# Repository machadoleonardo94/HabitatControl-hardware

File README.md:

## Hardware files for running HabitatControl Firmware
### ** Version 1 contains 5 PWM open drain channels, 2 NO relay channels, I2C 1" OLED display and DHT22 humidity and temperature sensor;
### ** Version 3 contains 6 PWM 700mA current limited LED drivers and I2C 1" OLED display
### Both versions are controlled via webserver for schedule of light intensity and data sampling

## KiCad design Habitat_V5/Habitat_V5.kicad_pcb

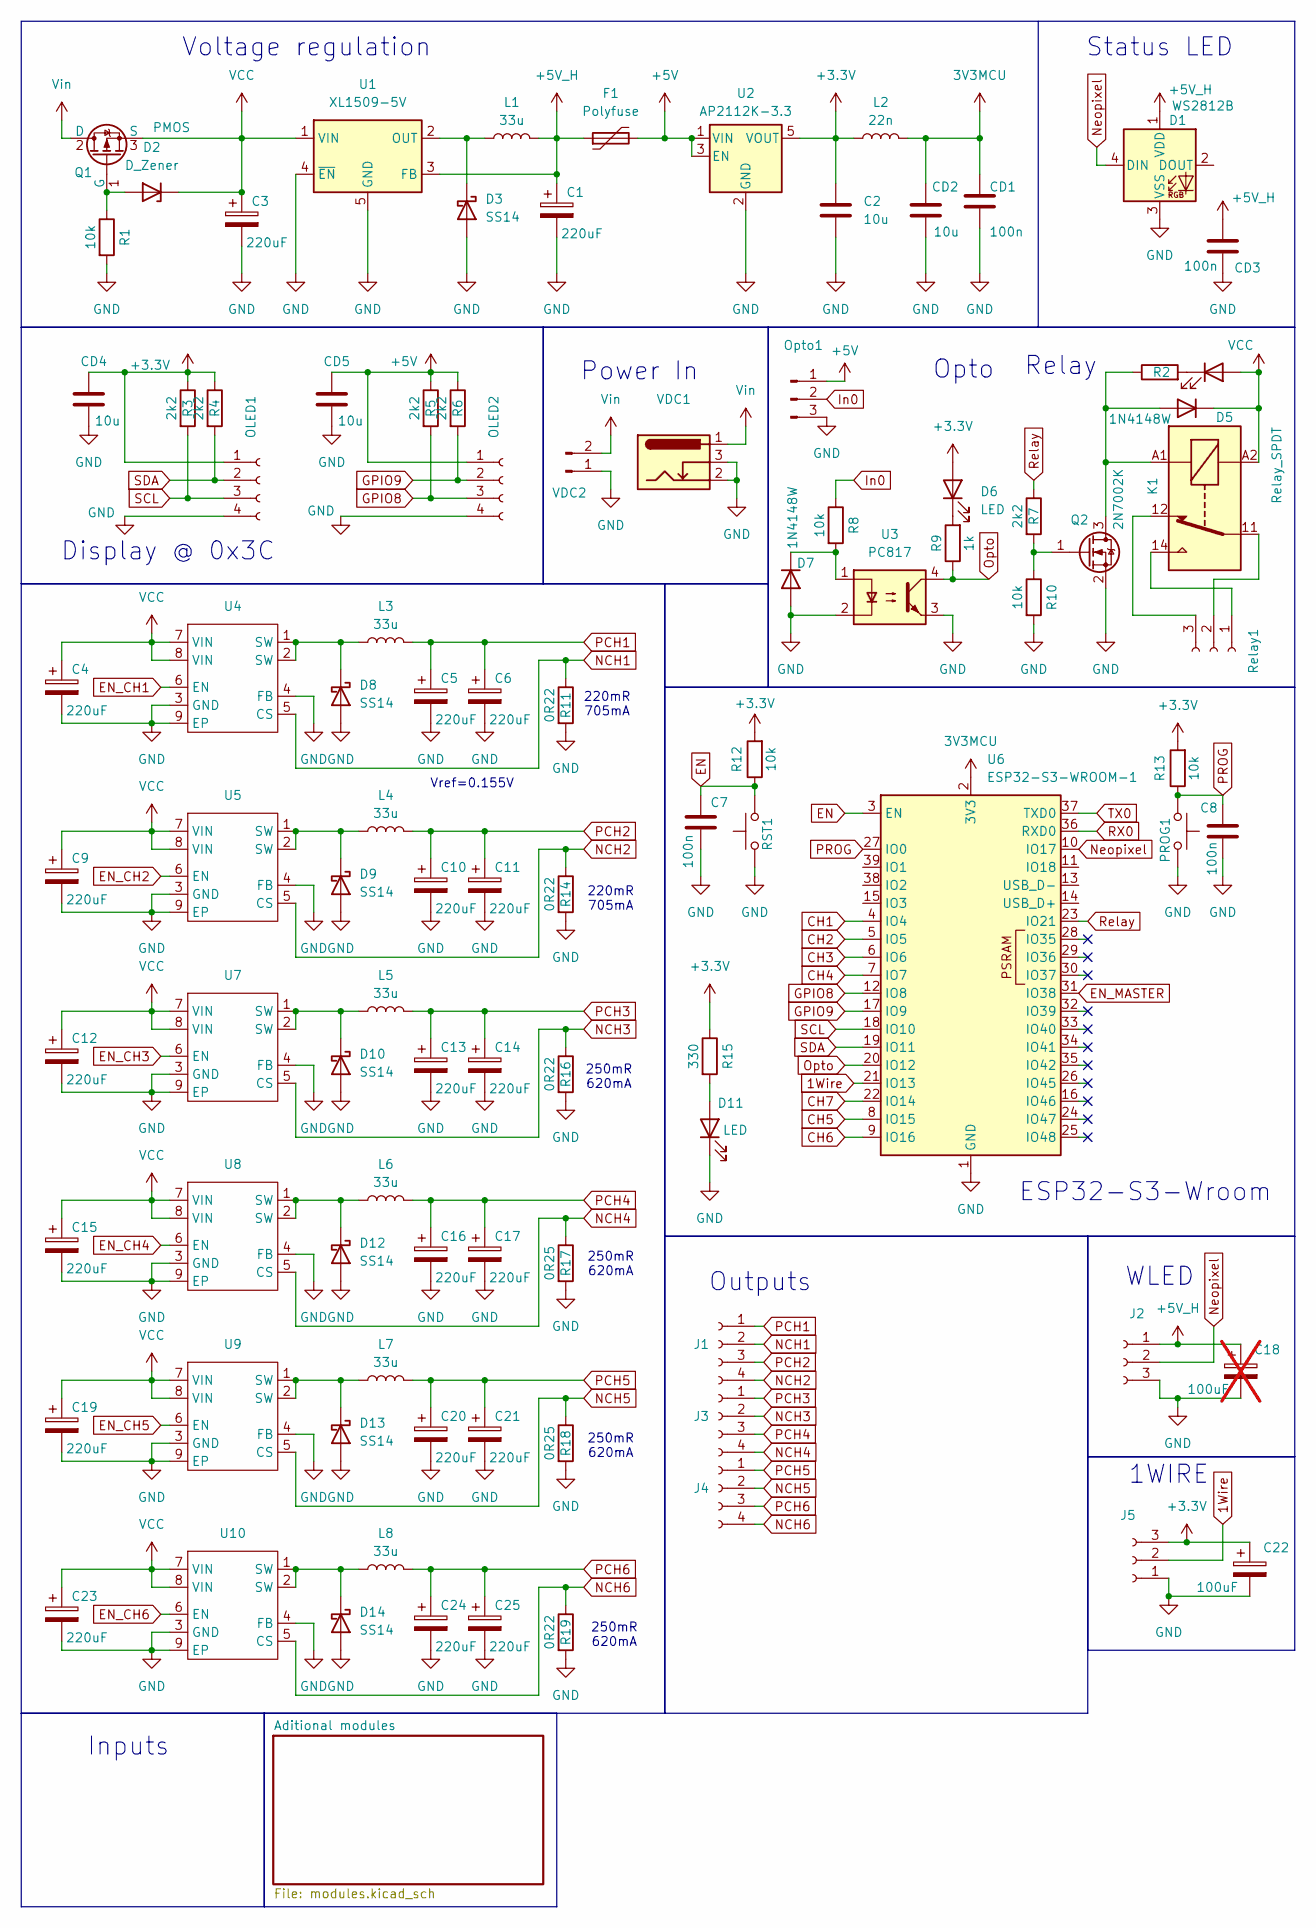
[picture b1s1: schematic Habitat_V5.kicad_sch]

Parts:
C1, C3, C4, C5, C6, C9, C10, C11, C12, C13, C14, C15, C16, C17, C19, C20, C21, C23, C24, C25: 220uF; C_Elec_6.3x7.7; LCSC C7471881
C2: 10u; C_0805_2012Metric; LCSC C77075
C7, C8: 100n; C_0805_2012Metric; LCSC C2909631
C18: 100uF; C_Elec_6.3x7.7; LCSC C99837; not fitted
C22: 100uF; C_Elec_6.3x7.7; LCSC C99837
CD1, CD3: 100n; C_0805_2012Metric; LCSC C2909631
CD2, CD4, CD5: 10u; C_0805_2012Metric; LCSC C77075
D1: WS2812B; LED_WS2812B_PLCC4_5.0x5.0mm_P3.2mm; LCSC 1
D2: D_Zener; D_MiniMELF; LCSC C181075
D3, D8, D9, D10, D12, D13, D14: SS14; D_SMA; LCSC C2909920
D4, D6, D11: LED; LED_0805_2012Metric_Pad1.15x1.40mm_HandSolder; LCSC C84256
D5, D7: 1N4148W; D_SOD-123; LCSC C82544
F1: Polyfuse; Fuse_1206_3216Metric_Pad1.42x1.75mm_HandSolder; LCSC C22446878
J1, J3, J4: Conn_01x04_Socket; PhoenixContact_MSTBA_2,5_4-G-5,08_1x04_P5.08mm_Horizontal
J2, J5: Conn_01x03_Socket; PhoenixContact_MSTBA_2,5_3-G-5,08_1x03_P5.08mm_Horizontal
K1: Relay_SPDT; Relay_SPDT_Hongfa_JQC-3FF_0XX-1Z
L1, L3, L4, L5, L6, L7, L8: 33u; L_Sunlord_SWPA4010S; LCSC C167885
L2: 22n; L_0805_2012Metric; LCSC C167885
OLED1, OLED2: Conn_01x04_Socket; Hirose_DF13C_CL535-0404-8-51_1x04-1MP_P1.25mm_Vertical; LCSC C7433470
Opto1: Conn_01x03_Pin; PhoenixContact_MSTBA_2,5_3-G-5,08_1x03_P5.08mm_Horizontal; LCSC 1
PROG1: SW_Push; SW_SPST_PTS647_Sx38; LCSC C455246
Q1: PMOS; SOT-223-3_TabPin2; LCSC C154901
Q2: 2N7002K; SOT-23; LCSC C65189
R1, R8, R10, R12, R13: 10k; R_0805_2012Metric; LCSC C17414
R2, R9: 1k; R_0805_2012Metric; LCSC C95781
R3, R4, R5, R6, R7: 2k2; R_0805_2012Metric; LCSC C17520
R11, R14, R16, R19: 0R22; R_1206_3216Metric; LCSC C2683384
R15: 330; R_0805_2012Metric; LCSC C17630
R17, R18: 0R25; R_1206_3216Metric; LCSC C2932845
RST1: SW_Push; SW_SPST_PTS647_Sx38; LCSC C455246
Relay1: Conn_01x03_Socket; PhoenixContact_MSTBA_2,5_3-G-5,08_1x03_P5.08mm_Horizontal
U1: XL1509-5V; SOIC-8_3.9x4.9mm_P1.27mm; LCSC C2681227
U2: AP2112K-3.3; SOT-23-5; LCSC C51118
U3: PC817; SMDIP-4_W7.62mm; LCSC C5451664
U4, U5, U7, U8, U9, U10: ESOP-8_L4.9-W3.9-P1.27-LS6.0-BL-EP; Manufacturer Part XL4001E1; LCSC Part Name XL4001E1
U6: ESP32-S3-WROOM-1
VDC1: Barrel_Jack_Switch; BarrelJack_Horizontal; LCSC C720557
VDC2: Conn_01x02_Pin; PhoenixContact_MSTBA_2,5_2-G-5,08_1x02_P5.08mm_Horizontal; LCSC 1

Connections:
1Wire: J5.2, U6.21 (IO13)
3V3MCU: CD1.1, CD2.1, L2.2, U6.2 (3V3)
+3.3V: C2.1, C22.1, CD4.1, D6.2 (A), J5.3, L2.1, OLED1.1, R3.1, R4.1, R12.2, R13.2, R15.1, U2.5 (VOUT); also elsewhere on the board
+5V: CD5.1, F1.2, OLED2.1, Opto1.1, R5.1, R6.1, U2.1 (VIN), U2.3 (EN); also elsewhere on the board
+5V_H: C1.1, C18.1, CD3.1, D1.1 (VDD), F1.1, J2.1, L1.2, U1.3 (FB)
CH1: U6.4 (IO4); also elsewhere on the board
CH2: U6.5 (IO5); also elsewhere on the board
CH3: U6.6 (IO6); also elsewhere on the board
CH4: U6.7 (IO7); also elsewhere on the board
CH5: U6.8 (IO15); also elsewhere on the board
CH6: U6.9 (IO16); also elsewhere on the board
CH7: U6.22 (IO14); also elsewhere on the board
EN: C7.1, R12.1, RST1.2, U6.3 (EN)
EN_CH1: U4.6 (EN); also elsewhere on the board
EN_CH2: U5.6 (EN); also elsewhere on the board
EN_CH3: U7.6 (EN); also elsewhere on the board
EN_CH4: U8.6 (EN); also elsewhere on the board
EN_CH5: U9.6 (EN); also elsewhere on the board
EN_CH6: U10.6 (EN); also elsewhere on the board
EN_MASTER: U6.31 (IO38); also elsewhere on the board
GND: C1.2, C2.2, C3.2, C4.2, C5.2, C6.2, C7.2, C8.2, C9.2, C10.2, C11.2, C12.2, C13.2, C14.2, C15.2, C16.2, C17.2, C18.2, C19.2, C20.2, C21.2, C22.2, C23.2, C24.2, C25.2, CD1.2, CD2.2, CD3.2, CD4.2, CD5.2, D1.3 (VSS), D3.2 (A), D7.2 (A), D8.2 (A), D9.2 (A), D10.2 (A), D11.1 (K), D12.2 (A), D13.2 (A), D14.2 (A), J2.3, J5.1, OLED1.4, OLED2.4, Opto1.3, PROG1.1, Q2.2 (S), R1.2, R10.2, R11.2, R14.2, R16.2, R17.2, R18.2, R19.2, RST1.1, U1.4 (~EN), U1.5 (GND), U1.6 (GND), U1.7 (GND), U1.8 (GND), U2.2 (GND), U3.2, U3.3, U4.3 (GND), U4.4 (FB), U4.9 (EP), U5.3 (GND), U5.4 (FB), U5.9 (EP), U6.1 (GND), U6.40 (GND), U6.41 (GND), U7.3 (GND), U7.4 (FB), U7.9 (EP), U8.3 (GND), U8.4 (FB), U8.9 (EP), U9.3 (GND), U9.4 (FB), U9.9 (EP), U10.3 (GND), U10.4 (FB), U10.9 (EP), VDC1.2, VDC1.3, VDC2.1; also elsewhere on the board
GPIO8: OLED2.3, R5.2, U6.12 (IO8)
GPIO9: OLED2.2, R6.2, U6.17 (IO9)
In0: Opto1.2, R8.1
NCH1: J1.2, R11.1, U4.5 (CS)
NCH2: J1.4, R14.1, U5.5 (CS)
NCH3: J3.2, R16.1, U7.5 (CS)
NCH4: J3.4, R17.1, U8.5 (CS)
NCH5: J4.2, R18.1, U9.5 (CS)
NCH6: J4.4, R19.1, U10.5 (CS)
Neopixel: D1.4 (DIN), J2.2, U6.10 (IO17)
unnamed: D2.2 (A), Q1.1 (G), R1.1
unnamed: D3.1 (K), L1.1, U1.2 (OUT)
unnamed: D4.1 (K), R2.2
unnamed: D5.2 (A), K1.A1, Q2.3 (D), R2.1
unnamed: D6.1 (K), R9.2
unnamed: D7.1 (K), R8.2, U3.1
unnamed: D8.1 (K), L3.1, U4.1 (SW), U4.2 (SW)
unnamed: D9.1 (K), L4.1, U5.1 (SW), U5.2 (SW)
unnamed: D10.1 (K), L5.1, U7.1 (SW), U7.2 (SW)
unnamed: D11.2 (A), R15.2
unnamed: D12.1 (K), L6.1, U8.1 (SW), U8.2 (SW)
unnamed: D13.1 (K), L7.1, U9.1 (SW), U9.2 (SW)
unnamed: D14.1 (K), L8.1, U10.1 (SW), U10.2 (SW)
unnamed: Q2.1 (G), R7.2, R10.1
unnamed: K1.14, Relay1.1
unnamed: K1.11, Relay1.2
unnamed: K1.12, Relay1.3
Opto: R9.1, U3.4, U6.20 (IO12)
PCH1: C5.1, C6.1, J1.1, L3.2
PCH2: C10.1, C11.1, J1.3, L4.2
PCH3: C13.1, C14.1, J3.1, L5.2
PCH4: C16.1, C17.1, J3.3, L6.2
PCH5: C20.1, C21.1, J4.1, L7.2
PCH6: C24.1, C25.1, J4.3, L8.2
PROG: C8.1, PROG1.2, R13.1, U6.27 (IO0)
RX0: U6.36 (RXD0); also elsewhere on the board
Relay: R7.1, U6.23 (IO21)
SCL: OLED1.3, R3.2, U6.18 (IO10); also elsewhere on the board
SDA: OLED1.2, R4.2, U6.19 (IO11); also elsewhere on the board
TX0: U6.37 (TXD0); also elsewhere on the board
VCC: C3.1, C4.1, C9.1, C12.1, C15.1, C19.1, C23.1, D2.1 (K), D4.2 (A), D5.1 (K), K1.A2, Q1.3 (S), U1.1 (VIN), U4.7 (VIN), U4.8 (VIN), U5.7 (VIN), U5.8 (VIN), U7.7 (VIN), U7.8 (VIN), U8.7 (VIN), U8.8 (VIN), U9.7 (VIN), U9.8 (VIN), U10.7 (VIN), U10.8 (VIN); also elsewhere on the board
Vin: Q1.2 (D), VDC1.1, VDC2.2

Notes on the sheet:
250mR 620mA
WLED
Power In
220mR 705mA
Status LED
ESP32-S3-Wroom
Display @ 0x3C
Outputs
Relay
Inputs
1WIRE
Voltage regulation
Vref=0.155V
Opto

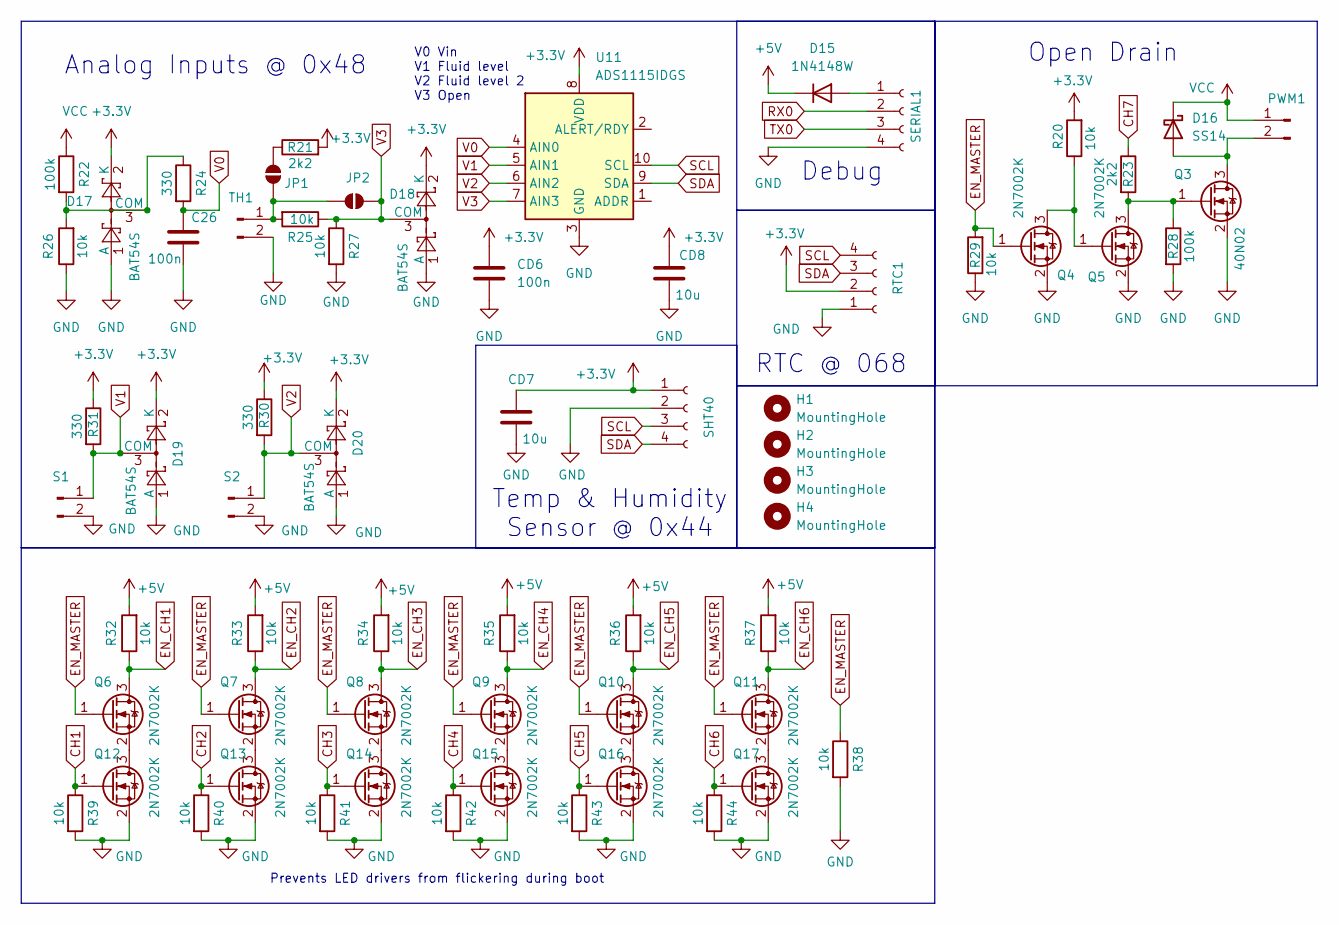
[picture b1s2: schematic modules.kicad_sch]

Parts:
C26: 100n; C_0805_2012Metric; LCSC C1711
CD6: 100n; C_0805_2012Metric; LCSC C1711
CD7, CD8: 10u; C_0805_2012Metric; LCSC C77075
D15: 1N4148W; D_SOD-123; LCSC C82544
D16: SS14; D_SMA; LCSC C2909920
D17, D18, D19, D20: BAT54S; SOT-23; LCSC C47546
H1, H2, H3, H4: MountingHole; MountingHole_3.2mm_M3
JP1, JP2: SolderJumper_2_Open; SolderJumper-2_P1.3mm_Open_RoundedPad1.0x1.5mm
PWM1: Conn_01x02_Pin; PhoenixContact_MSTBA_2,5_2-G-5,08_1x02_P5.08mm_Horizontal; LCSC 1
Q3: 40N02; TO-252-2
Q4, Q5, Q6, Q7, Q8, Q9, Q10, Q11, Q12, Q13, Q14, Q15, Q16, Q17: 2N7002K; SOT-23; LCSC C65189
R20, R25, R26, R27, R29, R32, R33, R34, R35, R36, R37, R38, R39, R40, R41, R42, R43, R44: 10k; R_0805_2012Metric; LCSC C17414
R21, R23: 2k2; R_0805_2012Metric; LCSC C17520
R22, R28: 100k; R_0805_2012Metric; LCSC C149504
R24, R30, R31: 330; R_0805_2012Metric; LCSC C17630
RTC1: Conn_01x04_Socket; RTC; LCSC 1
S1, S2: Conn_01x02_Pin; PhoenixContact_MSTBA_2,5_2-G-5,08_1x02_P5.08mm_Horizontal; LCSC 1
SERIAL1: Conn_01x04_Socket; Hirose_DF13C_CL535-0404-8-51_1x04-1MP_P1.25mm_Vertical; LCSC C7433470
SHT40: Conn_01x04_Socket; PinHeader_1x04_P2.54mm_Vertical; LCSC 1
TH1: Conn_01x02_Pin; PhoenixContact_MSTBA_2,5_2-G-5,08_1x02_P5.08mm_Horizontal; LCSC 1
U11: ADS1115IDGS; TSSOP-10_3x3mm_P0.5mm; LCSC C37593

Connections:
+3.3V: CD6.1, CD7.1, CD8.1, D17.2 (K), D18.2 (K), D19.2 (K), D20.2 (K), R20.2, R21.2, R30.1, R31.1, RTC1.2, SHT40.1, U11.8 (VDD); also elsewhere on the board
+5V: D15.1 (K), R32.2, R33.2, R34.2, R35.2, R36.2, R37.2; also elsewhere on the board
CH1: Q12.1 (G), R39.1; also elsewhere on the board
CH2: Q13.1 (G), R40.1; also elsewhere on the board
CH3: Q14.1 (G), R41.1; also elsewhere on the board
CH4: Q15.1 (G), R42.1; also elsewhere on the board
CH5: Q16.1 (G), R43.1; also elsewhere on the board
CH6: Q17.1 (G), R44.1; also elsewhere on the board
CH7: R23.1; also elsewhere on the board
EN_CH1: Q6.3 (D), R32.1; also elsewhere on the board
EN_CH2: Q7.3 (D), R33.1; also elsewhere on the board
EN_CH3: Q8.3 (D), R34.1; also elsewhere on the board
EN_CH4: Q9.3 (D), R35.1; also elsewhere on the board
EN_CH5: Q10.3 (D), R36.1; also elsewhere on the board
EN_CH6: Q11.3 (D), R37.1; also elsewhere on the board
EN_MASTER: Q4.1 (G), Q6.1 (G), Q7.1 (G), Q8.1 (G), Q9.1 (G), Q10.1 (G), Q11.1 (G), R29.2, R38.1; also elsewhere on the board
GND: C26.2, CD6.2, CD7.2, CD8.2, D17.1 (A), D18.1 (A), D19.1 (A), D20.1 (A), Q3.2 (S), Q4.2 (S), Q5.2 (S), Q12.2 (S), Q13.2 (S), Q14.2 (S), Q15.2 (S), Q16.2 (S), Q17.2 (S), R26.1, R27.2, R28.2, R29.1, R38.2, R39.2, R40.2, R41.2, R42.2, R43.2, R44.2, RTC1.1, S1.2, S2.2, SERIAL1.4, SHT40.2, TH1.2, U11.3 (GND); also elsewhere on the board
unnamed: D15.2 (A), SERIAL1.1
unnamed: D16.2 (A), PWM1.2, Q3.3 (D)
unnamed: D17.3 (COM), R22.2, R24.1, R26.2
unnamed: JP1.1 (A), JP2.1 (A), R25.2, TH1.1
unnamed: JP1.2 (B), R21.1
unnamed: Q3.1 (G), Q5.3 (D), R23.2, R28.1
unnamed: Q4.3 (D), Q5.1 (G), R20.1
unnamed: Q10.2 (S), Q16.3 (D)
unnamed: Q11.2 (S), Q17.3 (D)
unnamed: Q6.2 (S), Q12.3 (D)
unnamed: Q7.2 (S), Q13.3 (D)
unnamed: Q8.2 (S), Q14.3 (D)
unnamed: Q9.2 (S), Q15.3 (D)
RX0: SERIAL1.2; also elsewhere on the board
SCL: RTC1.4, SHT40.3, U11.10 (SCL); also elsewhere on the board
SDA: RTC1.3, SHT40.4, U11.9 (SDA); also elsewhere on the board
TX0: SERIAL1.3; also elsewhere on the board
V0: C26.1, R24.2, U11.4 (AIN0)
V1: D19.3 (COM), R31.2, S1.1, U11.5 (AIN1)
V2: D20.3 (COM), R30.2, S2.1, U11.6 (AIN2)
V3: D18.3 (COM), JP2.2 (B), R25.1, R27.1, U11.7 (AIN3)
VCC: D16.1 (K), PWM1.1, R22.1; also elsewhere on the board

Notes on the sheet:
Analog Inputs @ 0x48
RTC @ 068
Debug
Open Drain
Prevents LED drivers from flickering during boot
Temp & Humidity Sensor @ 0x44
V0 Vin V1 Fluid level V2 Fluid level 2 V3 Open

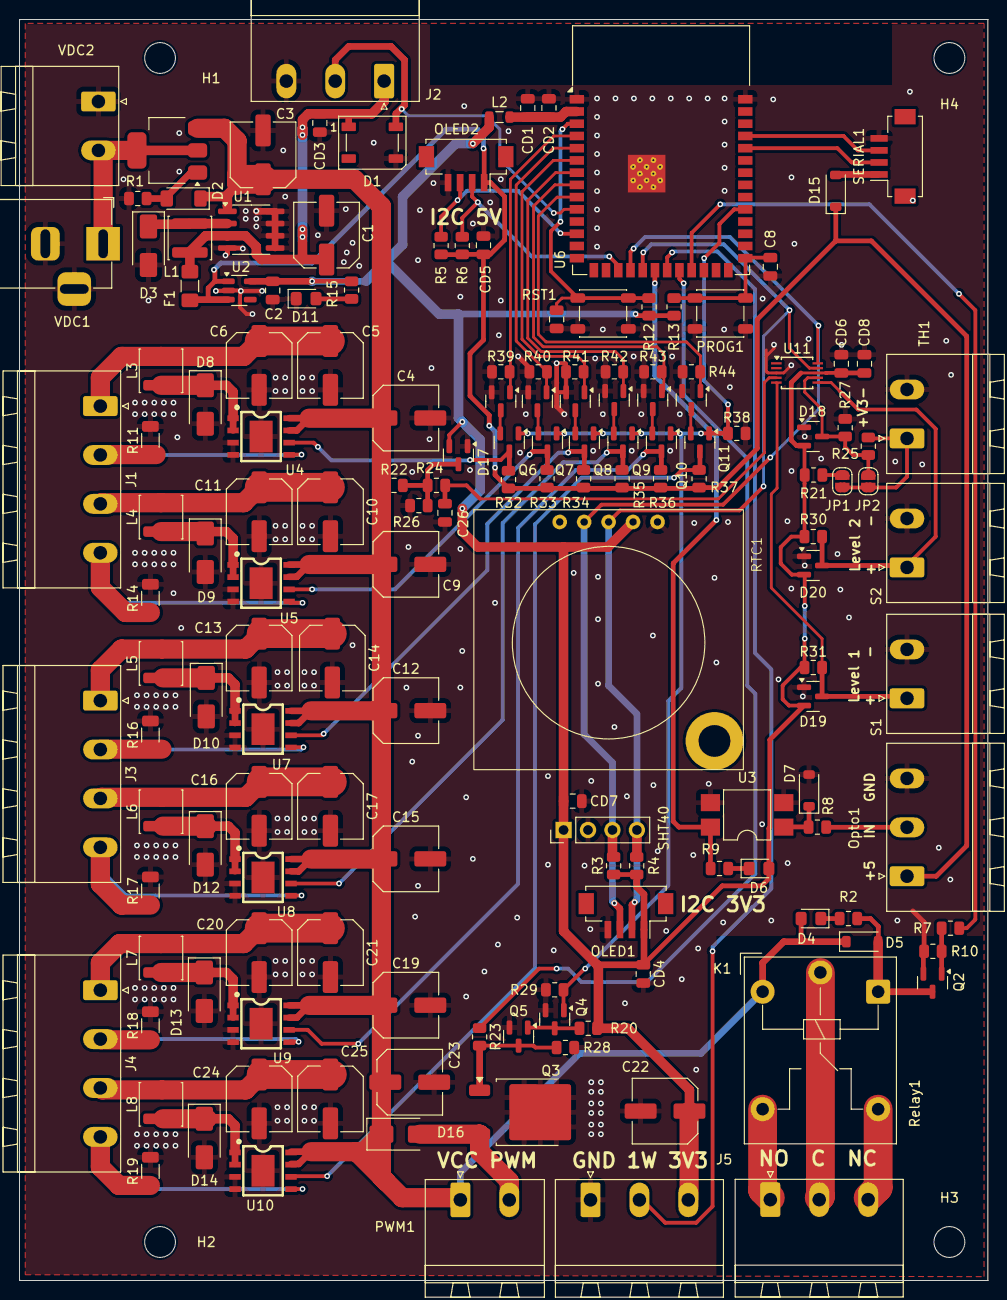
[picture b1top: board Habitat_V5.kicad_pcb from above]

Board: 2 copper layers, 100.6 x 131.0 mm, 161 parts (0 on the bottom side), 80 nets.

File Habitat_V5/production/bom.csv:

Designator,Footprint,Quantity,Value,LCSC Part #
"C1, C10, C11, C12, C13, C14, C15, C16, C17, C19, C20, C21, C23, C24, C25, C3, C4, C5, C6, C9",C_Elec_6.3x7.7,20,220uF,C7471881
"C2, CD2, CD4, CD5, CD7, CD8",0805,6,10u,C77075
C22,C_Elec_6.3x7.7,1,100uF,C99837
"C26, CD6",0805,2,100n,C1711
"C7, C8, CD1, CD3",0805,4,100n,C2909631
D1,LED_WS2812B_PLCC4_5.0x5.0mm_P3.2mm,1,WS2812B,1
"D10, D12, D13, D14, D16, D3, D8, D9",D_SMA,8,SS14,C2909920
"D11, D4, D6",0805,3,LED,C84256
"D15, D5, D7",D_SOD-123,3,1N4148W,C82544
"D17, D18, D19, D20",SOT-23,4,BAT54S,C47546
D2,D_MiniMELF,1,D_Zener,C181075
F1,1206,1,Polyfuse,C22446878
"J1, J3, J4","PhoenixContact_MSTBA_2,5_4-G-5,08_1x04_P5.08mm_Horizontal",3,Conn_01x04_Socket,
"J2, J5, RELAY1","PhoenixContact_MSTBA_2,5_3-G-5,08_1x03_P5.08mm_Horizontal",3,Conn_01x03_Socket,
K1,Relay_SPDT_Hongfa_JQC-3FF_0XX-1Z,1,Relay_SPDT,
"L1, L3, L4, L5, L6, L7, L8",L_Sunlord_SWPA4010S,7,33u,C167885
L2,0805,1,22n,C167885
"OLED1, OLED2, SERIAL1",Hirose_DF13C_CL535-0404-8-51_1x04-1MP_P1.25mm_Vertical,3,Conn_01x04_Socket,C7433470
OPTO1,"PhoenixContact_MSTBA_2,5_3-G-5,08_1x03_P5.08mm_Horizontal",1,Conn_01x03_Pin,1
"PROG1, RST1",SW_SPST_PTS647_Sx38,2,SW_Push,C455246
"PWM1, S1, S2, TH1, VDC2","PhoenixContact_MSTBA_2,5_2-G-5,08_1x02_P5.08mm_Horizontal",5,Conn_01x02_Pin,1
Q1,SOT-223-3_TabPin2,1,PMOS,C154901
"Q10, Q11, Q12, Q13, Q14, Q15, Q16, Q17, Q2, Q4, Q5, Q6, Q7, Q8, Q9",SOT-23,15,2N7002K,C65189
Q3,TO-252-2,1,40N02,
"R1, R10, R12, R13, R20, R25, R26, R27, R29, R32, R33, R34, R35, R36, R37, R38, R39, R40, R41, R42, R43, R44, R8",0805,23,10k,C17414
"R11, R14, R16, R19",1206,4,0R22,C2683384
"R15, R24, R30, R31",0805,4,330,C17630
"R17, R18",1206,2,0R25,C2932845
"R2, R9",0805,2,1k,C95781
"R21, R23, R3, R4, R5, R6, R7",0805,7,2k2,C17520
"R22, R28",0805,2,100k,C149504
RTC1,RTC,1,Conn_01x04_Socket,1
SHT40,PinHeader_1x04_P2.54mm_Vertical,1,Conn_01x04_Socket,1
U1,SOIC-8_3.9x4.9mm_P1.27mm,1,XL1509-5V,C2681227
"U10, U4, U5, U7, U8, U9",ESOP-8_L4.9-W3.9-P1.27-LS6.0-BL-EP,6,~,C2988027
U11,TSSOP-10_3x3mm_P0.5mm,1,ADS1115IDGS,C37593
U2,SOT-23-5,1,AP2112K-3.3,C51118
U3,SMDIP-4_W7.62mm,1,PC817,C5451664
U6,ESP32-S3-WROOM-1,1,ESP32-S3-WROOM-1,
VDC1,BarrelJack_Horizontal,1,Barrel_Jack_Switch,C720557

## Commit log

2020-06-23 First push
    Primeira versão do esquemático para testes
2020-07-03 Update modulo de acionamento.dch
    Esquemático definitivo
2020-07-03 Backup
    Major layout wiring
2020-07-04 Layout V1.0
    Versão completa submetida para revisão
2020-07-04 Update Habitat_layout.dip
    Revisão do buraco da antena no layout
2020-07-04 Adição do Encoder
2020-07-05 Update Habitat_layout.dip
    Revisão do silk
2020-07-06 Conector HB-9500
    Atualização de todos os conectores de potência;
    Nova malha de potência;
    Redução de mosfets redundantes;
    Relay alterado local na placa de estufa;
    Relays em curto alterados (para NO);
2020-07-11 Atualização dos conectores, espaçamento métrico
    Entrada de potência alterada KRE2 5mm para KF7.62
    PCB redimensionada de acordo
    Todas as dimensões no sistema métrico
    Grid e largura das trilhas em imperial
    Tamanho final: 105x109mm
    Furos M3 em (3.5,105), (80,105), (25,3.5)
2020-07-11 Gerber commit
    Posicionamento da logo no botton silk
2020-07-11 Gerber com silk atualizada
2020-07-16 Valor dos componentes
2020-07-16 Step files and silk
    Pra modelagem 3D
2020-08-06 Correção de tamanho dos furos pro BS9500
2023-03-22 V2 submited for review
    5x 12V 3A open drain PWM channels
    5x 3V3 outputs for external driver
    2x Relay
    1x I2C Temperature sensor
    1x I2C output (display)
    1x 5V 2A output (cooling fan)
2023-03-23 Rework on Power traces
    PVin line thickness 70 -> 90
    GND vias rearranjed
2023-03-23 Final revision before production
2023-03-30 Habitat_V2_sanity-check
    Update before factory submission
    *Replaced 7.62mm header to barrier block;
    * Added varistor to AC line;
    * External panel fuse is expected;
2023-03-30 Sanity check before factory
2023-04-10 Thermal and network rework
    Switched power mosfets to SOT-89;
    ESP antenna moved to board edge;
    Added optocoupled level-shifter as additional module.
2023-04-14 Heatsink update
    Added copper planes to act as heatsinks. Not great, not terrible
2023-04-14 Minor copper pour updates
2023-12-21 V3 schematic and layout
2023-12-21 Removed temp files
2023-12-21 V3 update
2023-12-22 HArdware update
2024-02-26 Hardware fixes
    * Altered 2k2 resistors to 3k3
    * Corrected reverse voltage protection
    * Swapped B540C diodes for SS14
    * Swapped 47uH 3A inductor for 33uH 1A
2024-03-02 V4 start
2024-06-10 Update for 5ch and nice caps
2024-06-10 Files for production
2024-06-18 Added levelshifter
2024-06-18 Added level shifter and fabrication files
2024-06-18 Added series limiting resistor for inverters
2025-07-17 Added V5 for ESP32
2025-07-18 Current update
2025-07-23 Updated PCB and Schematic
2025-07-24 Validation pre fab
    Pls check
2025-07-24 Added final schematic PDF
    To do: correct GPIO pinout docs
2025-07-24 Review for production
